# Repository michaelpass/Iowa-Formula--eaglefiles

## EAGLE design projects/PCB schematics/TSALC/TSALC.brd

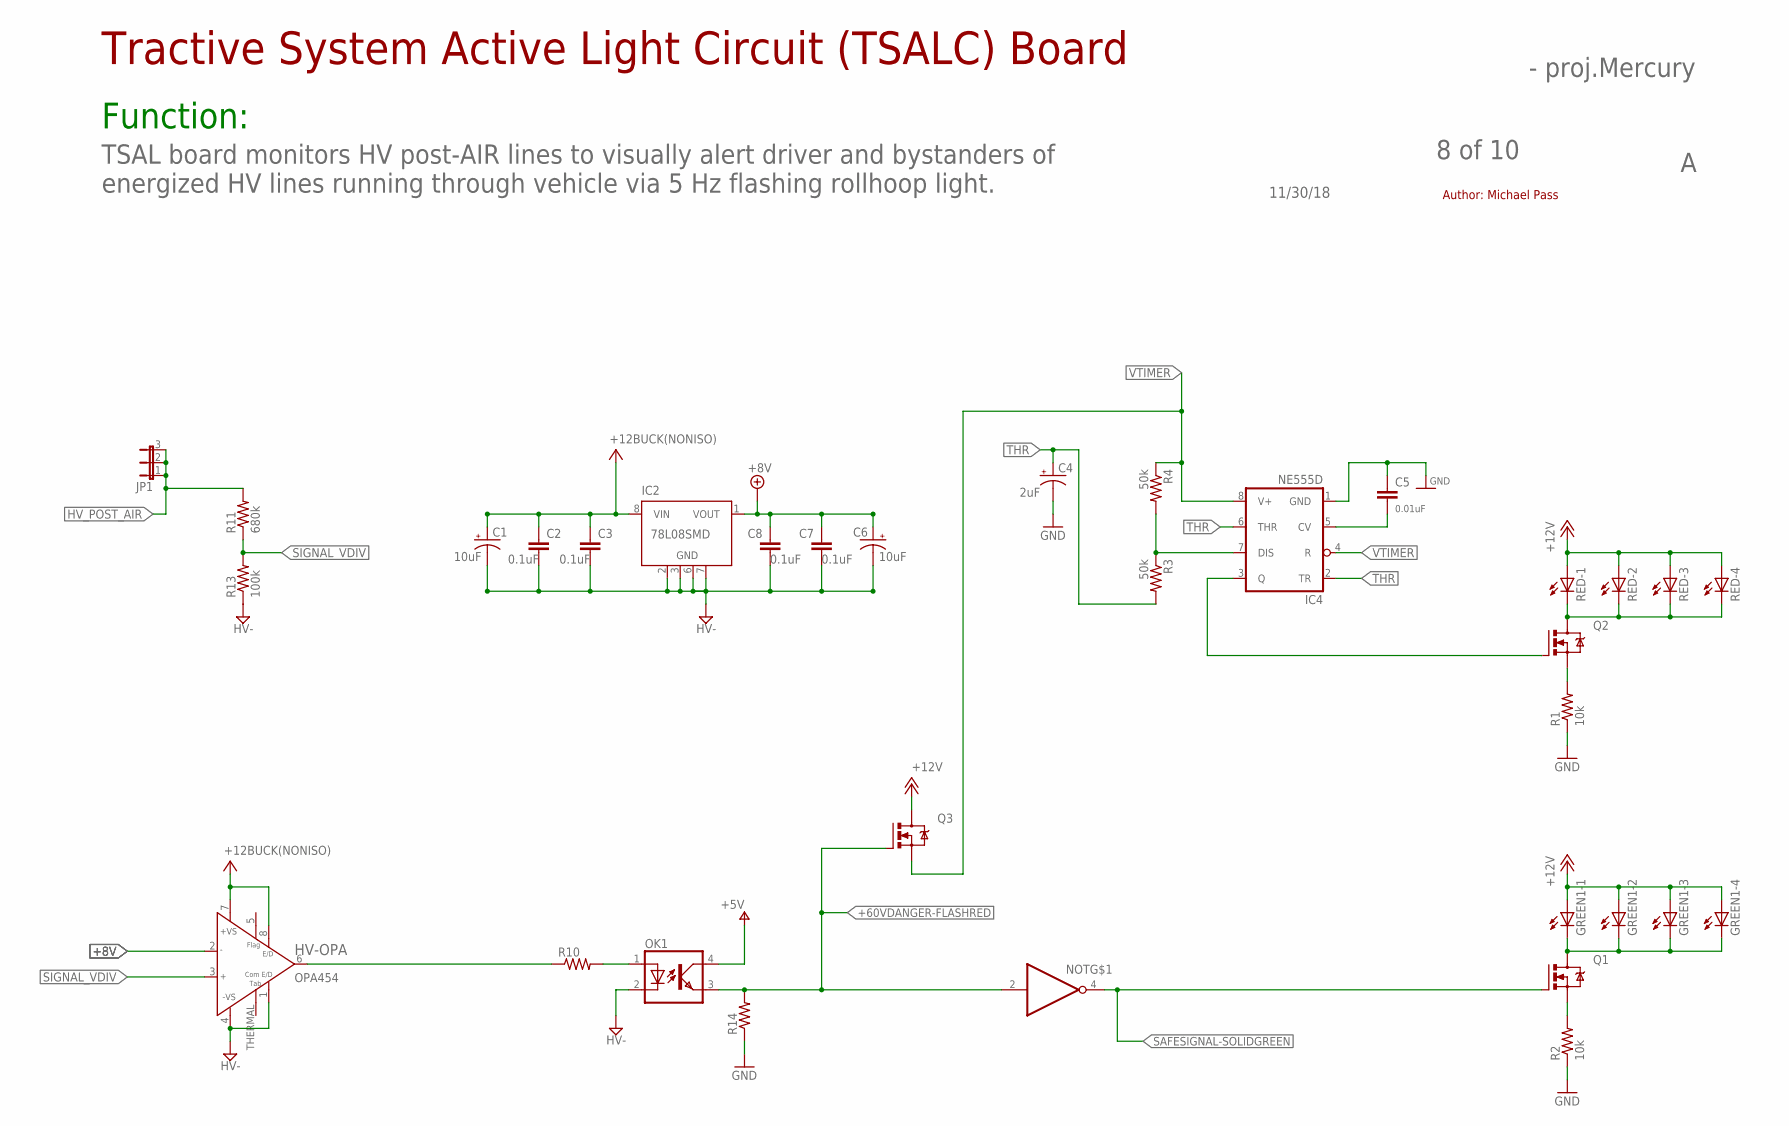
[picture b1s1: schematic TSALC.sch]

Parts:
C1, C6: 10uF; 085CS_1AW
C2, C3, C7, C8: 0.1uF; C0805
C4: 2uF; 085CS_1AW
C5: 0.01uF; C0805
GREEN1: LZR184
HV-OPA: OPA454; SO08GP
IC2: 78L08SMD; SO08
IC4: NE555D; SO08
JP1: JP2W
NOT: 74LVC1G06DCK; SC70-5
OK1: PC817-S; SOP04(2.54)
Q1, Q2, Q3: IRLZ44Z; TO220BH
R1, R2: 10k; R0805
R3, R4: 50k; R0805
R10, R14: R-US_R0805; R0805
R11: 680k; R0805
R13: 100k; R0805
RED: LZR184

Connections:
+8V: C6.+, C7.1, C8.1, HV-OPA.2 (IN-), IC2.1 (VOUT)
+12V: GREEN1.A1 (A), GREEN1.A2 (A), GREEN1.A3 (A), GREEN1.A4 (A), Q3.D, RED.A1 (A), RED.A2 (A), RED.A3 (A), RED.A4 (A)
+60VDANGER-FLASHRED: NOT.2 (I), OK1.3 (EMIT), Q3.G, R14.2
GND: C4.-, C5.1, IC4.1 (GND), OK1.2 (C), R1.1, R2.1, R13.1, R14.1
HV-: C1.-, C2.2, C3.2, C6.-, C7.2, C8.2, HV-OPA.1 (E/DCOM), HV-OPA.4 (-VS), IC2.2 (GND), IC2.3 (GND), IC2.6 (GND), IC2.7 (GND), NOT.3 (GND)
HV_POST_AIR: JP1.1, JP1.2, JP1.3, R11.2
unnamed: IC4.7 (DIS), R3.1, R4.2
unnamed: GREEN1.K1 (C), GREEN1.K2 (C), GREEN1.K3 (C), GREEN1.K4 (C), Q1.D
unnamed: Q1.S, R2.2
unnamed: Q2.D, RED.K1 (C), RED.K2 (C), RED.K3 (C), RED.K4 (C)
unnamed: Q2.S, R1.2
unnamed: C5.2, IC4.5 (CV)
unnamed: IC4.3 (Q), Q2.G
unnamed: HV-OPA.6 (OUT), R10.1
unnamed: OK1.1 (A), R10.2
SAFESIGNAL-SOLIDGREEN: NOT.4 (O), Q1.G
SIGNAL_VDIV: HV-OPA.3 (IN+), R11.1, R13.2
THR: C4.+, IC4.2 (TR), IC4.6 (THR), R3.2
V+: C1.+, C2.1, C3.1, HV-OPA.7 (+VS), HV-OPA.8 (E/D), IC2.8 (VIN), OK1.4 (COL)
VCC: NOT.5 (VCC)
VTIMER: IC4.4 (R), IC4.8 (V+), Q3.S, R4.1

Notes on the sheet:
Tractive System Active Light Circuit (TSALC) Board
Function:
11/30/18
8 of 10
- proj.Mercury
TSAL board monitors HV post-AIR lines to visually alert driver and bystanders of energized HV lines running through vehicle via 5 Hz flashing rollhoop light.
Author: Michael Pass

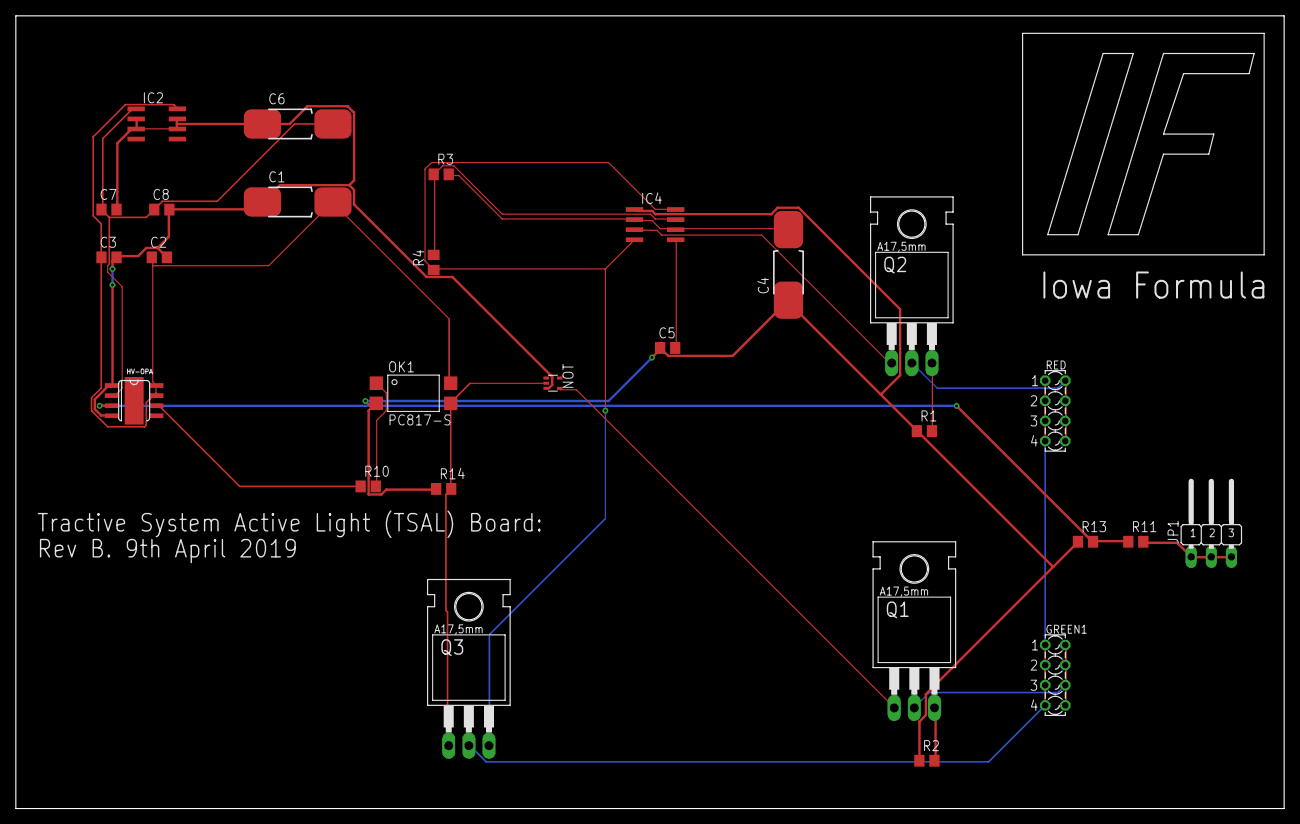
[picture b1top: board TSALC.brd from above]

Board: 2 copper layers, 160.0 x 100.0 mm, 27 parts (0 on the bottom side), 20 nets.

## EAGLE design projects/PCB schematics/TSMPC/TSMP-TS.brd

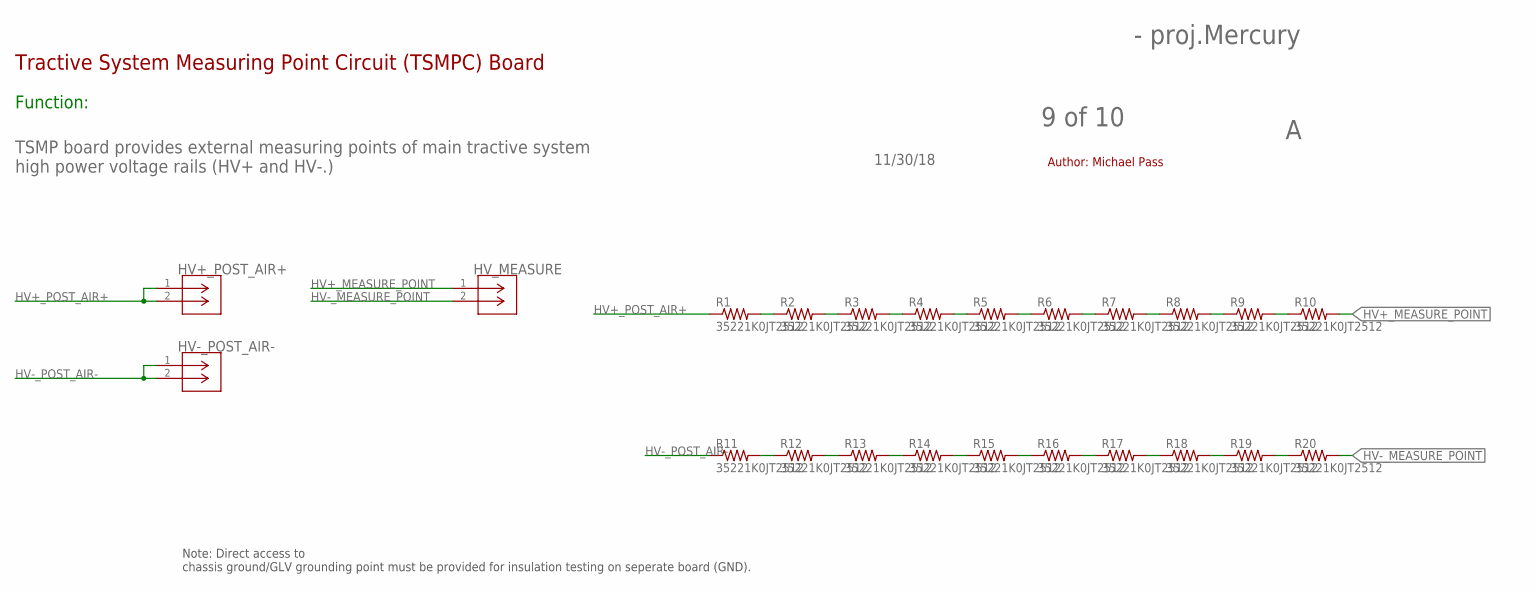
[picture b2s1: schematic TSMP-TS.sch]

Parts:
HV+_POST_AIR+: 2P_1-770166-0; CON2_1X2_P163_VMNL-1MTG
HV-_POST_AIR-: 2P_1-770166-0; CON2_1X2_P163_VMNL-1MTG
HV_MEASURE: 2P_1-770166-0; CON2_1X2_P163_VMNL-1MTG
R1, R2, R3, R4, R5, R6, R7, R8, R9, R10, R11, R12, R13, R14, R15, R16, R17, R18, R19, R20: 35221K0JT2512; R2512

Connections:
HV+_MEASURE_POINT: HV_MEASURE.1, R10.2
HV+_POST_AIR+: HV+_POST_AIR+.1, HV+_POST_AIR+.2, R1.1
HV-_MEASURE_POINT: HV_MEASURE.2, R20.2
HV-_POST_AIR-: HV-_POST_AIR-.1, HV-_POST_AIR-.2, R11.1
unnamed: R1.2, R2.1
unnamed: R2.2, R3.1
unnamed: R3.2, R4.1
unnamed: R4.2, R5.1
unnamed: R5.2, R6.1
unnamed: R6.2, R7.1
unnamed: R7.2, R8.1
unnamed: R8.2, R9.1
unnamed: R9.2, R10.1
unnamed: R11.2, R12.1
unnamed: R12.2, R13.1
unnamed: R13.2, R14.1
unnamed: R14.2, R15.1
unnamed: R15.2, R16.1
unnamed: R16.2, R17.1
unnamed: R17.2, R18.1
unnamed: R18.2, R19.1
unnamed: R19.2, R20.1

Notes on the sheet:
Tractive System Measuring Point Circuit (TSMPC) Board
Function:
11/30/18
9 of 10
- proj.Mercury
TSMP board provides external measuring points of main tractive system high power voltage rails (HV+ and HV-.)
Author: Michael Pass
Note: Direct access to chassis ground/GLV grounding point must be provided for insulation testing on seperate board (GND).

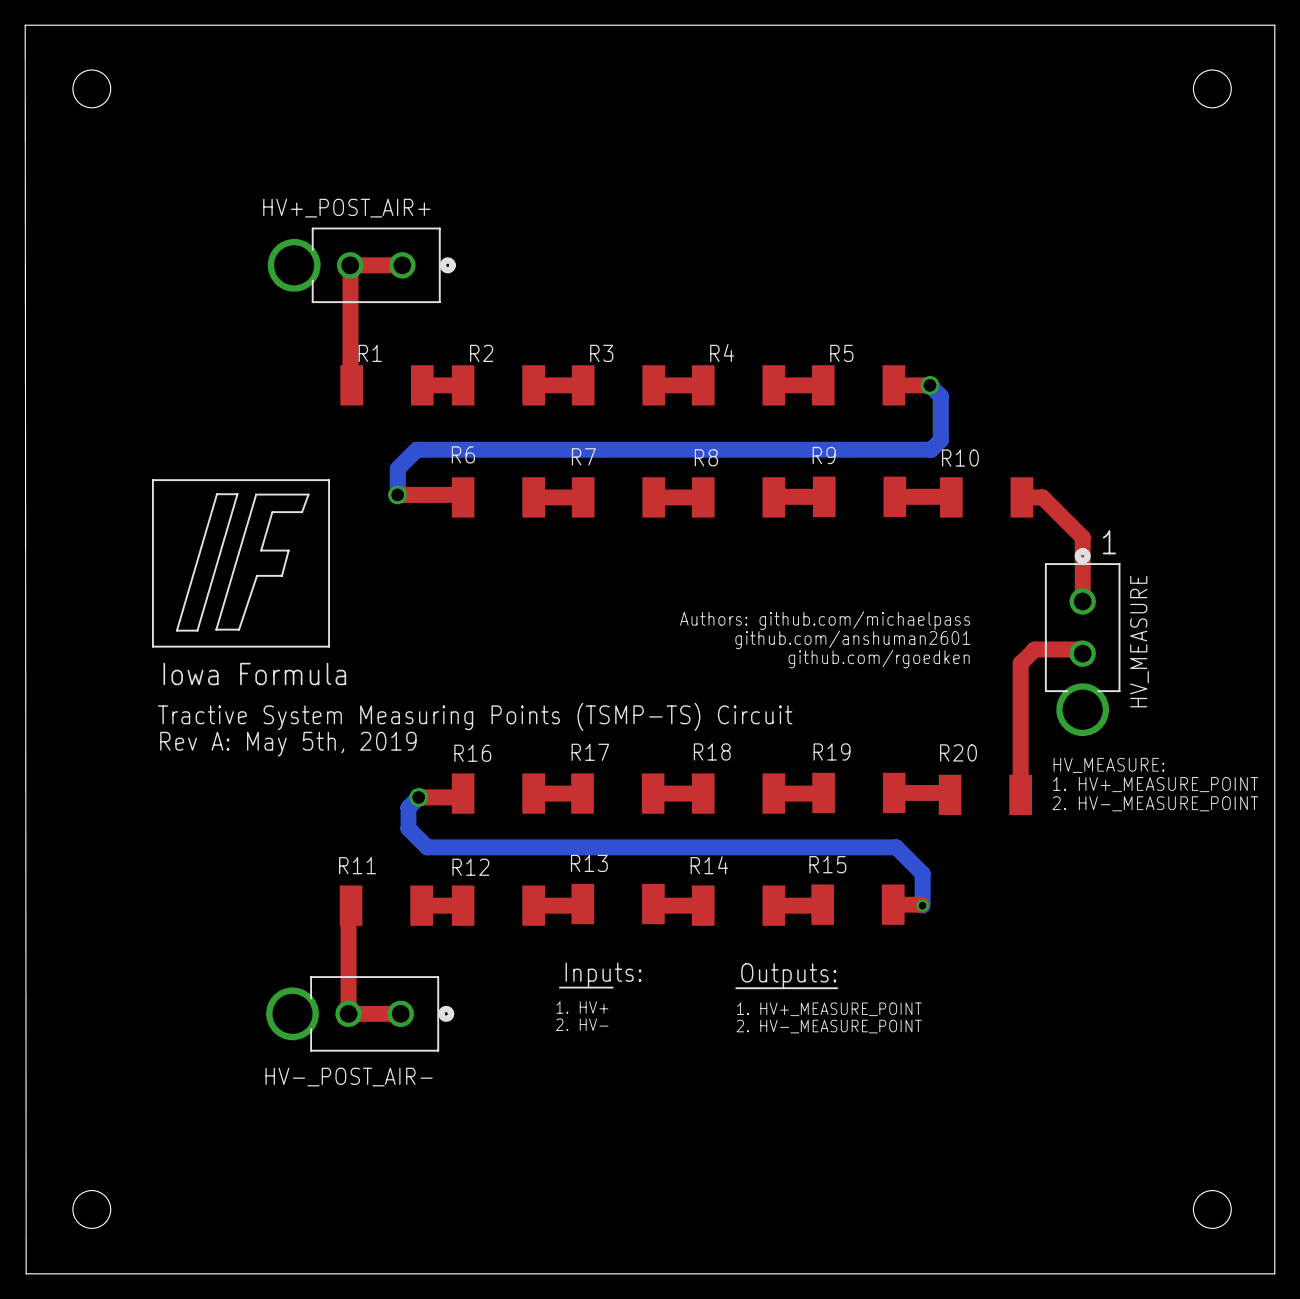
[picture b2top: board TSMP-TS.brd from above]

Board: 2 copper layers, 99.1 x 99.1 mm, 23 parts (0 on the bottom side), 22 nets.

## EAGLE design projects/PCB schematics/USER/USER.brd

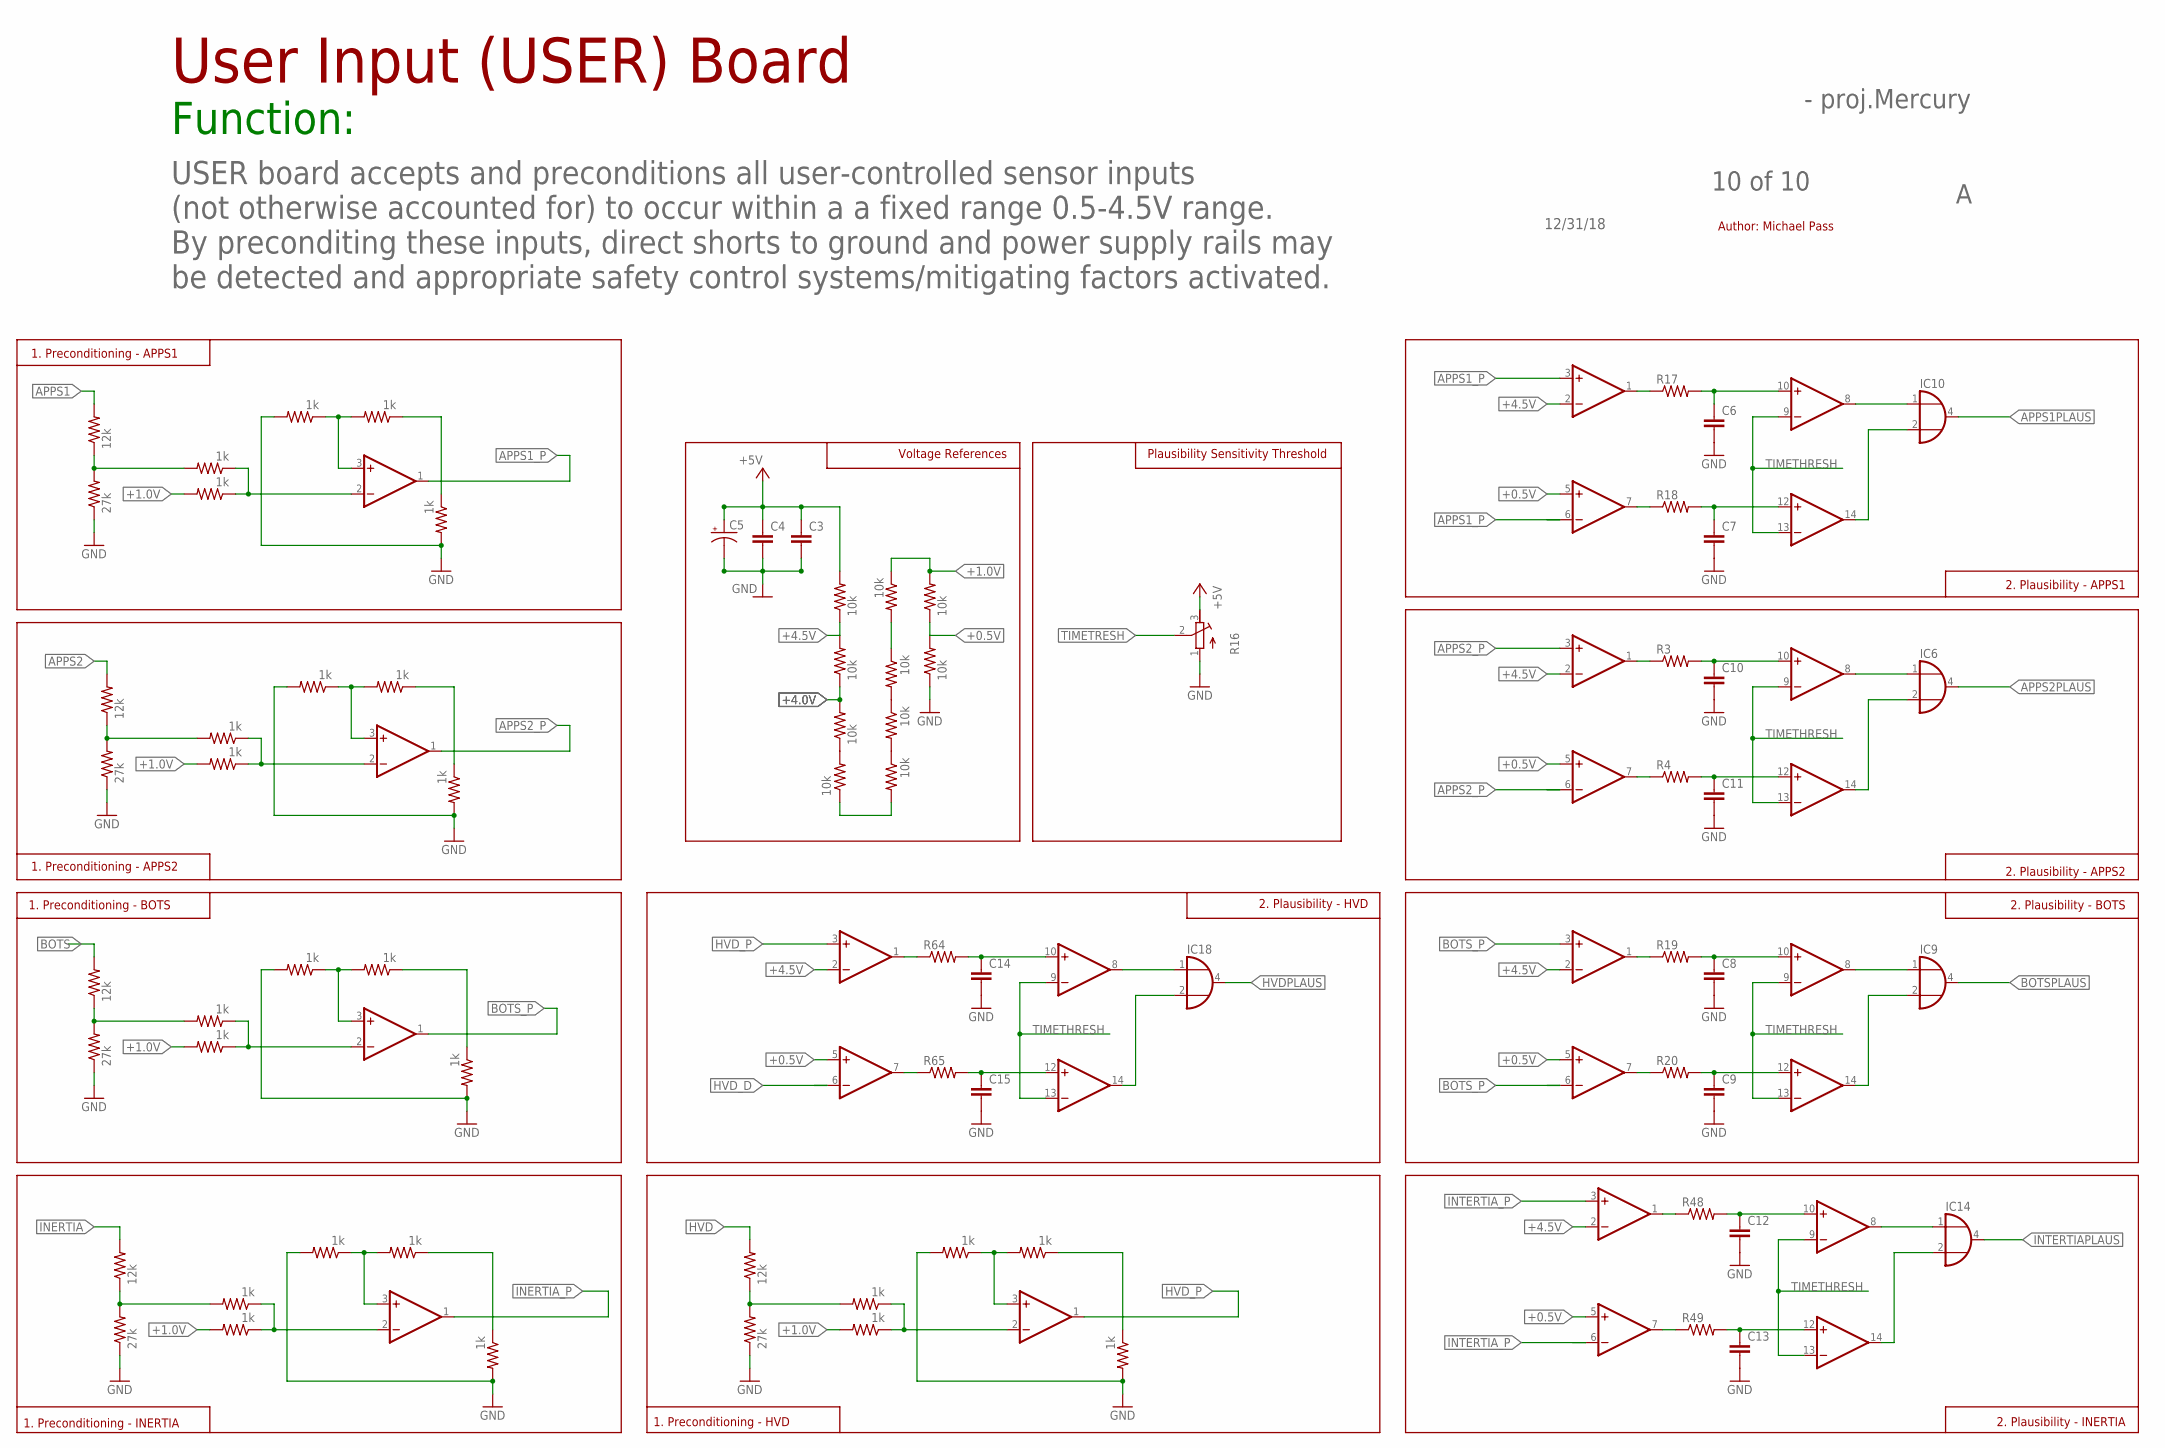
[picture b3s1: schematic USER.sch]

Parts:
C3, C4, C6, C7, C8, C9, C10, C11, C12, C13, C14, C15: C-EUC0805; C0805
C5: CPOL-US085CS-1AR; 085CS_1AR
IC1, IC3, IC4, IC5, IC7, IC8, IC13, IC17, IC19, IC20: OP11D; SO14
IC6, IC9, IC10, IC14, IC18: 74AHC1G32DCK; SC70-5
R1, R7, R71, R78, R85: 12k; R0805
R2, R21, R72, R79, R86: 27k; R0805
R3, R4, R17, R18, R19, R20, R48, R49, R64, R65: R-US_R0805; R0805
R5, R6, R8, R9, R10, R11, R12, R13, R14, R15: 10k; R0805
R16: R-TRIMM3224X; RTRIM3224X
R22, R23, R24, R25, R26, R66, R67, R68, R69, R70, R73, R74, R75, R76, R77, R80, R81, R82, R83, R84, R87, R88, R89, R90, R91: 1k; R0805

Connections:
+0.5V: IC1.5 (+IN), IC4.5 (+IN), IC5.5 (+IN), IC13.5 (+IN), IC17.5 (+IN), R14.1, R15.2
+1.0V: R13.1, R14.2, R23.2, R67.2, R74.2, R81.2, R88.2
+4.0V: R6.1, R8.2
+4.5V: IC1.2 (-IN), IC4.2 (-IN), IC5.2 (-IN), IC13.2 (-IN), IC17.2 (-IN), R5.1, R6.2
+5V: C3.1, C4.1, C5.+, R5.2, R16.3 (E)
APPS1: R71.2
APPS1PLAUS: IC10.4 (O)
APPS1_P: IC5.3 (+IN), IC5.6 (-IN), IC7.1 (OUT)
APPS2: R78.2
APPS2PLAUS: IC6.4 (O)
APPS2_P: IC1.3 (+IN), IC1.6 (-IN), IC19.1 (OUT)
BOTS: R7.2
BOTSPLAUS: IC9.4 (O)
BOTS_P: IC4.3 (+IN), IC4.6 (-IN), IC8.1 (OUT)
GND: C3.2, C4.2, C5.-, C6.2, C7.2, C8.2, C9.2, C10.2, C11.2, C12.2, C13.2, C14.2, C15.2, IC6.3 (GND), IC9.3 (GND), IC10.3 (GND), IC14.3 (GND), IC18.3 (GND), R2.1, R15.1, R16.1 (A), R21.1, R24.2, R26.2, R68.2, R70.2, R72.1, R75.2, R77.2, R79.1, R82.2, R84.2, R86.1, R89.2, R91.2
HVD: R85.2
HVDPLAUS: IC18.4 (O)
HVD_D: IC17.6 (-IN)
HVD_P: IC17.3 (+IN), IC20.1 (OUT)
INERTIA: R1.2
INERTIA_P: IC3.1 (OUT)
INTERTIAPLAUS: IC14.4 (O)
INTERTIA_P: IC13.3 (+IN), IC13.6 (-IN)
unnamed: IC3.3 (+IN), R68.1, R69.2
unnamed: R8.1, R9.2
unnamed: IC4.1 (OUT), R19.1
unnamed: R9.1, R10.2
unnamed: R11.1, R12.2
unnamed: IC5.1 (OUT), R17.1
unnamed: R12.1, R13.2
unnamed: R1.1, R2.2, R66.2
unnamed: R10.1, R11.2
unnamed: R69.1, R70.1
unnamed: IC3.2 (-IN), R66.1, R67.1
unnamed: C6.1, IC5.10 (+IN), R17.2
unnamed: C7.1, IC5.12 (+IN), R18.2
unnamed: IC5.7 (OUT), R18.1
unnamed: IC1.1 (OUT), R3.1
unnamed: C10.1, IC1.10 (+IN), R3.2
unnamed: C11.1, IC1.12 (+IN), R4.2
unnamed: IC1.7 (OUT), R4.1
unnamed: C8.1, IC4.10 (+IN), R19.2
unnamed: C9.1, IC4.12 (+IN), R20.2
unnamed: IC4.7 (OUT), R20.1
unnamed: IC1.8 (OUT), IC6.1 (I0)
unnamed: IC1.14 (OUT), IC6.2 (I1)
unnamed: IC8.3 (+IN), R24.1, R25.2
unnamed: R7.1, R21.2, R22.2
unnamed: R25.1, R26.1
unnamed: IC8.2 (-IN), R22.1, R23.1
unnamed: IC4.8 (OUT), IC9.1 (I0)
unnamed: IC4.14 (OUT), IC9.2 (I1)
unnamed: IC13.1 (OUT), R48.1
unnamed: C12.1, IC13.10 (+IN), R48.2
unnamed: IC7.3 (+IN), R75.1, R76.2
unnamed: R71.1, R72.2, R73.2
unnamed: IC5.8 (OUT), IC10.1 (I0)
unnamed: IC5.14 (OUT), IC10.2 (I1)
unnamed: C13.1, IC13.12 (+IN), R49.2
unnamed: IC13.7 (OUT), R49.1
unnamed: IC13.8 (OUT), IC14.1 (I0)
unnamed: IC13.14 (OUT), IC14.2 (I1)
unnamed: IC17.1 (OUT), R64.1
unnamed: C14.1, IC17.10 (+IN), R64.2
unnamed: C15.1, IC17.12 (+IN), R65.2
unnamed: IC17.7 (OUT), R65.1
unnamed: IC17.8 (OUT), IC18.1 (I0)
unnamed: IC17.14 (OUT), IC18.2 (I1)
unnamed: R76.1, R77.1
unnamed: IC7.2 (-IN), R73.1, R74.1
unnamed: IC19.3 (+IN), R82.1, R83.2
unnamed: R78.1, R79.2, R80.2
unnamed: R83.1, R84.1
unnamed: IC19.2 (-IN), R80.1, R81.1
unnamed: IC20.3 (+IN), R89.1, R90.2
unnamed: R85.1, R86.2, R87.2
unnamed: R90.1, R91.1
unnamed: IC20.2 (-IN), R87.1, R88.1
TIMETHRESH: IC1.9 (-IN), IC1.13 (-IN), IC4.9 (-IN), IC4.13 (-IN), IC5.9 (-IN), IC5.13 (-IN), IC13.9 (-IN), IC13.13 (-IN), IC17.9 (-IN), IC17.13 (-IN)
TIMETRESH: R16.2 (S)
V+: IC1.4 (V+), IC3.4 (V+), IC4.4 (V+), IC5.4 (V+), IC7.4 (V+), IC8.4 (V+), IC13.4 (V+), IC17.4 (V+), IC19.4 (V+), IC20.4 (V+)
V-: IC1.11 (V-), IC3.11 (V-), IC4.11 (V-), IC5.11 (V-), IC7.11 (V-), IC8.11 (V-), IC13.11 (V-), IC17.11 (V-), IC19.11 (V-), IC20.11 (V-)
VCC: IC6.5 (VCC), IC9.5 (VCC), IC10.5 (VCC), IC14.5 (VCC), IC18.5 (VCC)

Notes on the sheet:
12/31/18
10 of 10
- proj.Mercury
User Input (USER) Board
Function:
USER board accepts and preconditions all user-controlled sensor inputs (not otherwise accounted for) to occur within a a fixed range 0.5-4.5V range. By preconditing these inputs, direct shorts to ground and power supply rails may be detected and appropriate safety control systems/mitigating factors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
1. Preconditioning - APPS1
1. Preconditioning - APPS2
1. Preconditioning - BOTS
1. Preconditioning - INERTIA
1. Preconditioning - HVD
2. Plausibility - HVD
Voltage References
Plausibility Sensitivity Threshold
2. Plausibility - APPS1
2. Plausibility - APPS2
2. Plausibility - BOTS
2. Plausibility - INERTIA
Author: Michael Pass

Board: 2 copper layers, 84 parts (0 on the bottom side), 70 nets, no tracks yet.
